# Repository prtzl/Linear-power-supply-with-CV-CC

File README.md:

# Linear-power-supply-with-CC-CV

 Self made Linear power supply based on ThePostApocalypticInventor's work. Details in schematic and readme.
  
I made this schematic based on The Post Apocalyptic Inventor's work, that you can find in his chanel https://www.youtube.com/channel/UCDbWmfrwmzn1ZsGgrYRUxoA

This power supply design has been rewritten, tested and built by me and in the future, there will be pictures and videos of the finished project.

The power supply is very simple to make and to understand, so for any questions you can visit his video (https://www.youtube.com/watch?v=_CFIovMkRyg) describing all parts of the power supply. Feel free to ask him or me for advice.

Also this project involves mains power and mishandling of it can be fatal so make sure that you know that are you doing, buy premade mains components, such as the transformer and mains input with **fuse**.
## Warning
 **I am not responsible for any damage to your equipment or your health so study the circuit, and if you work with wiring your own mains part, make sure that you know what you are doing and so at your own risk.**
  
  Happy making! :P

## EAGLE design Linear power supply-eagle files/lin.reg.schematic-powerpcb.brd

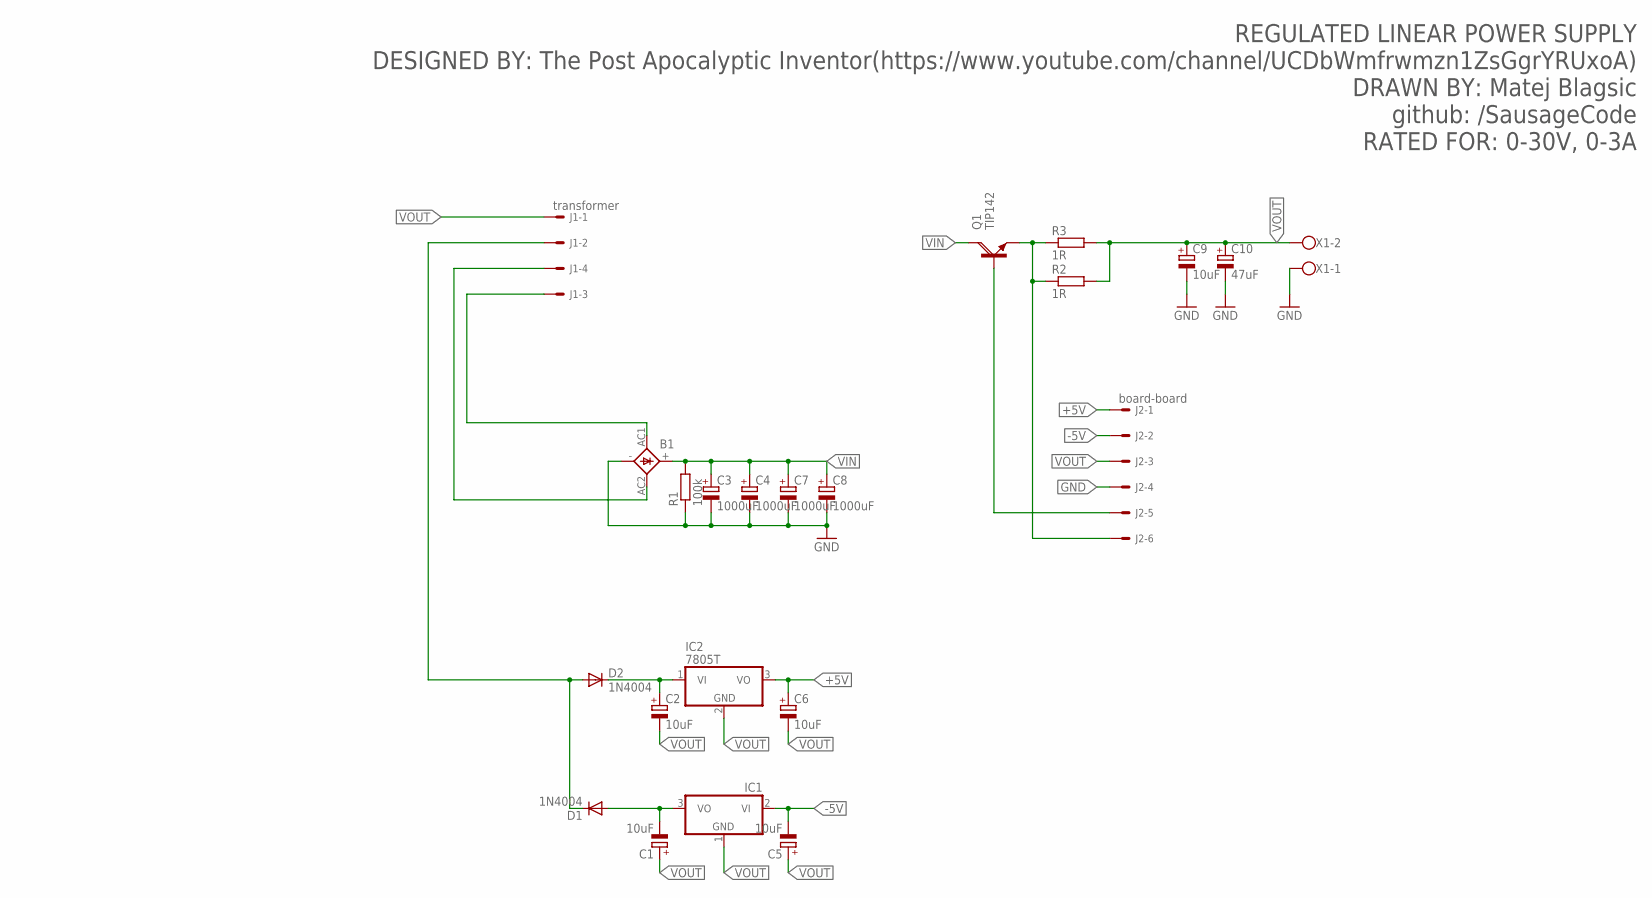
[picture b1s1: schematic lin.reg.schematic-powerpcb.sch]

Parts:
B1: 2KBB-R
C1, C2, C5, C6, C9: 10uF; E2-5
C3, C4, C7, C8: 1000uF; E5-13
C10: 47uF; E2-5
D1, D2: 1N4004; DO41-10
IC1: 7905T; TO220H
IC2: 7805T; TO220H
J1: transformer; 6410-04
J2: board-board; 6410-06
Q1: TIP142; SOT93
R1: 100k; 0309/12
R2, R3: 1R; 0922/22
X1: W237-102

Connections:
+5V: C6.+, IC2.3 (VO), J2.1
-5V: C5.-, IC1.2 (VI), J2.2
GND: B1.-, C3.-, C4.-, C7.-, C8.-, C9.-, C10.-, J2.4, R1.1, X1.1
unnamed: J2.6, Q1.E, R2.1, R3.1
unnamed: J2.5, Q1.B
unnamed: C2.+, D2.C, IC2.1 (VI)
unnamed: C1.-, D1.A, IC1.3 (VO)
unnamed: D1.C, D2.A, J1.2
unnamed: B1.AC2, J1.4
unnamed: B1.AC1, J1.3
VIN: B1.+, C3.+, C4.+, C7.+, C8.+, Q1.C, R1.2
VOUT: C1.+, C2.-, C5.+, C6.-, C9.+, C10.+, IC1.1 (GND), IC2.2 (GND), J1.1, J2.3, R2.2, R3.2, X1.2

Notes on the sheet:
REGULATED LINEAR POWER SUPPLY DESIGNED BY: The Post Apocalyptic Inventor(https://www.youtube.com/channel/UCDbWmfrwmzn1ZsGgrYRUxoA) DRAWN BY: Matej Blagsic github: /SausageCode RATED FOR: 0-30V, 0-3A

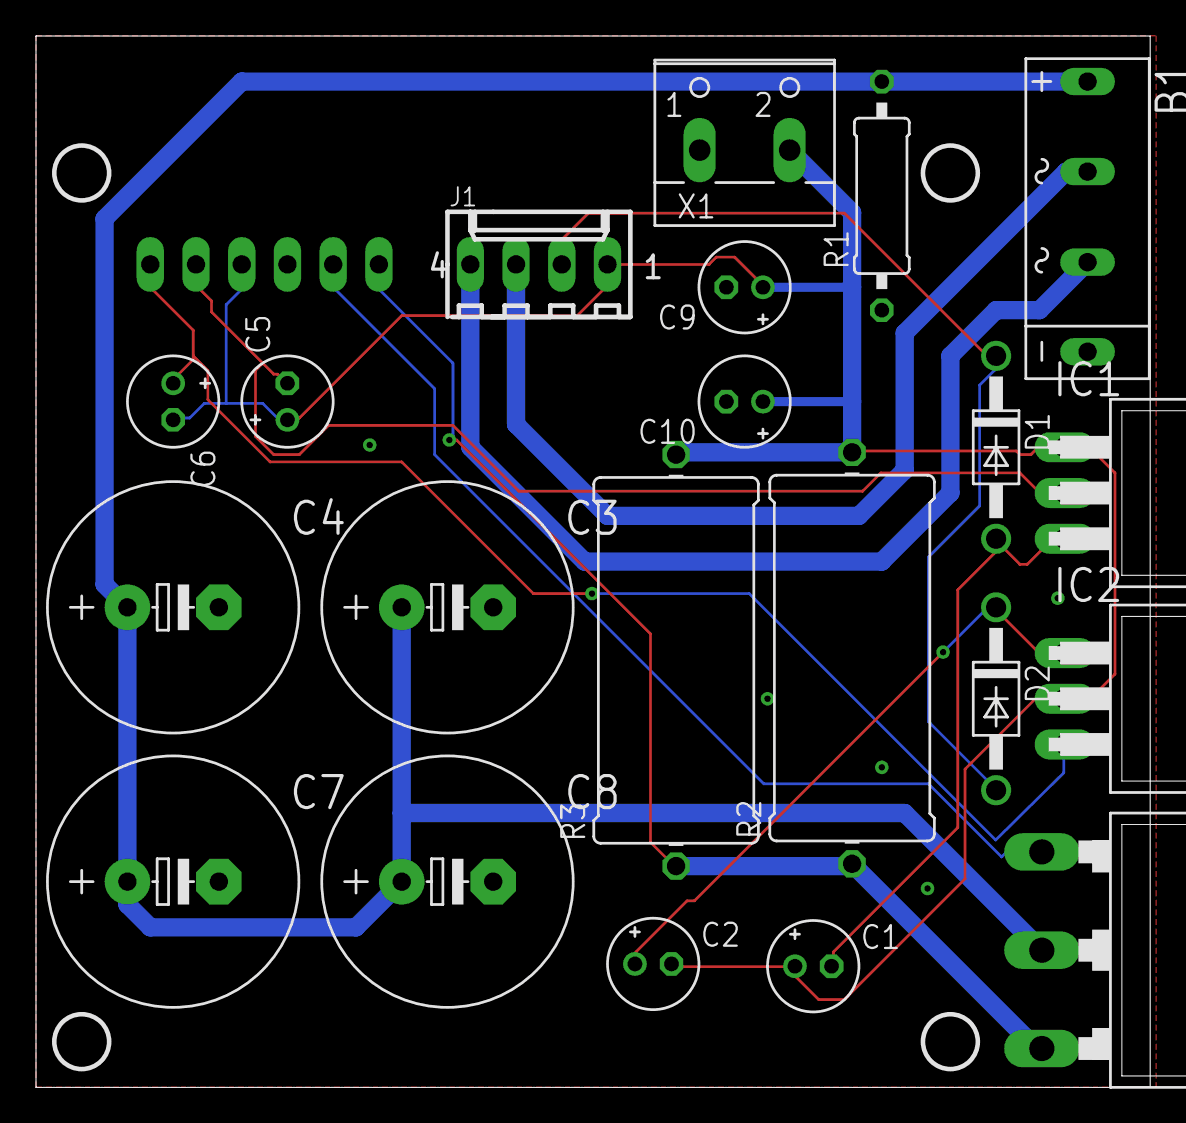
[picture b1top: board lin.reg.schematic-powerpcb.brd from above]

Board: 2 copper layers, 61.9 x 58.4 mm, 22 parts (1 on the bottom side), 12 nets.

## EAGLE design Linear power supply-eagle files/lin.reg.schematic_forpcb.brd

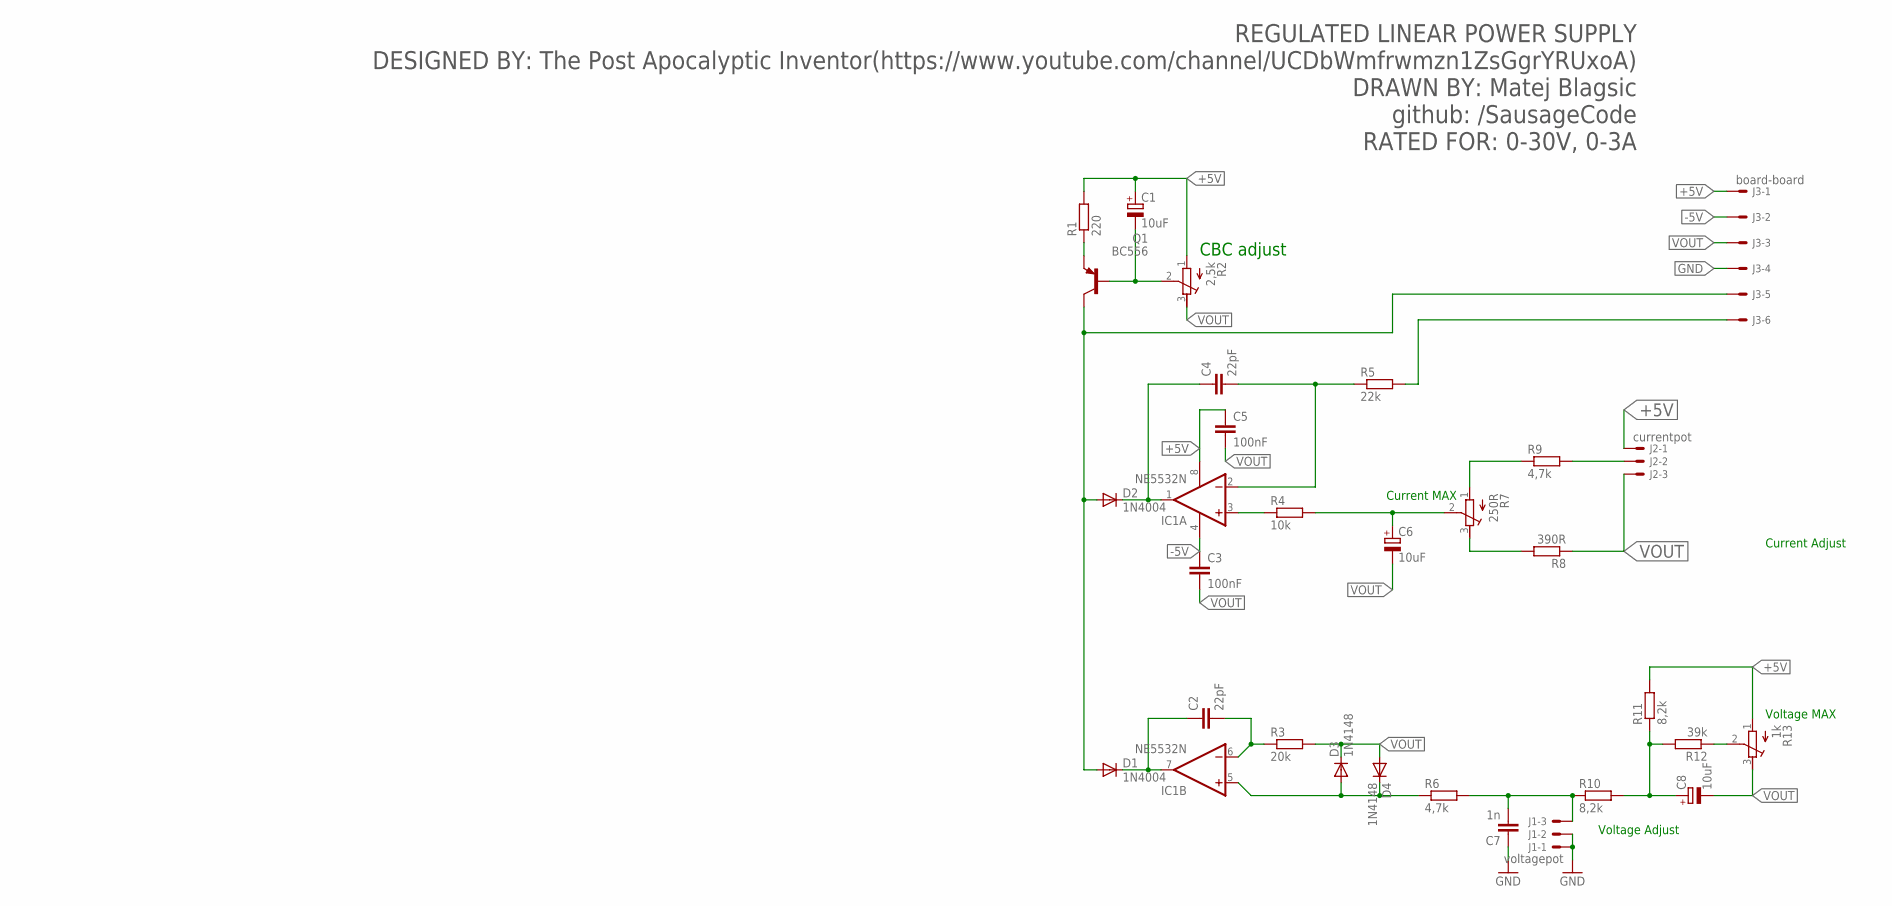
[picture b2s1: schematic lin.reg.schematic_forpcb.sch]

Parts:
C1, C6, C8: 10uF; E2,5-5
C2, C4: 22pF; C025-025X050
C3, C5: 100nF; C025-025X050
C7: 1n; C025-025X050
D1, D2: 1N4004; DO41-10
D3, D4: 1N4148; DO41-10
IC1: NE5532N; DIL08
J1: voltagepot; 6410-03
J2: currentpot; 6410-03
J3: board-board; 6410-06
Q1: BC556; TO92-EBC
R1: 220; 0207/10
R2: 2,5k; RTRIM64W
R3: 20k; 0207/10
R4: 10k; 0207/10
R5: 22k; 0207/10
R6, R9: 4,7k; 0207/10
R7: 250R; RTRIM64W
R8: 390R; 0207/10
R10, R11: 8,2k; 0207/10
R12: 39k; 0207/10
R13: 1k; RTRIM64W

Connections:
+5V: C1.+, C5.1, IC1.8 (V+), J2.1, J3.1, R1.2, R2.1 (A), R11.2, R13.1 (A)
-5V: C3.1, IC1.4 (V-), J3.2
GND: C7.1, J1.1, J1.2, J3.4
unnamed: C1.-, Q1.B, R2.2 (S)
unnamed: Q1.E, R1.1
unnamed: R7.1 (A), R9.1
unnamed: C4.1, D2.C, IC1.1 (OUT)
unnamed: C2.1, D1.C, IC1.7 (OUT)
unnamed: D1.A, D2.A, J3.5, Q1.C
unnamed: C2.2, IC1.6 (-IN), R3.1
unnamed: IC1.3 (+IN), R4.1
unnamed: D3.A, D4.C, IC1.5 (+IN), R6.1
unnamed: R7.3 (E), R8.2
unnamed: J2.2, R9.2
unnamed: C6.+, R4.2, R7.2 (S)
unnamed: C4.2, IC1.2 (-IN), R5.1
unnamed: C7.2, J1.3, R6.2, R10.1
unnamed: C8.+, R10.2, R11.1, R12.2
unnamed: R12.1, R13.2 (S)
unnamed: J3.6, R5.2
VOUT: C3.2, C5.2, C6.-, C8.-, D3.C, D4.A, J2.3, J3.3, R2.3 (E), R3.2, R8.1, R13.3 (E)

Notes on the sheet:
Voltage Adjust
Voltage MAX
Current Adjust
Current MAX
REGULATED LINEAR POWER SUPPLY DESIGNED BY: The Post Apocalyptic Inventor(https://www.youtube.com/channel/UCDbWmfrwmzn1ZsGgrYRUxoA) DRAWN BY: Matej Blagsic github: /SausageCode RATED FOR: 0-30V, 0-3A
CBC adjust

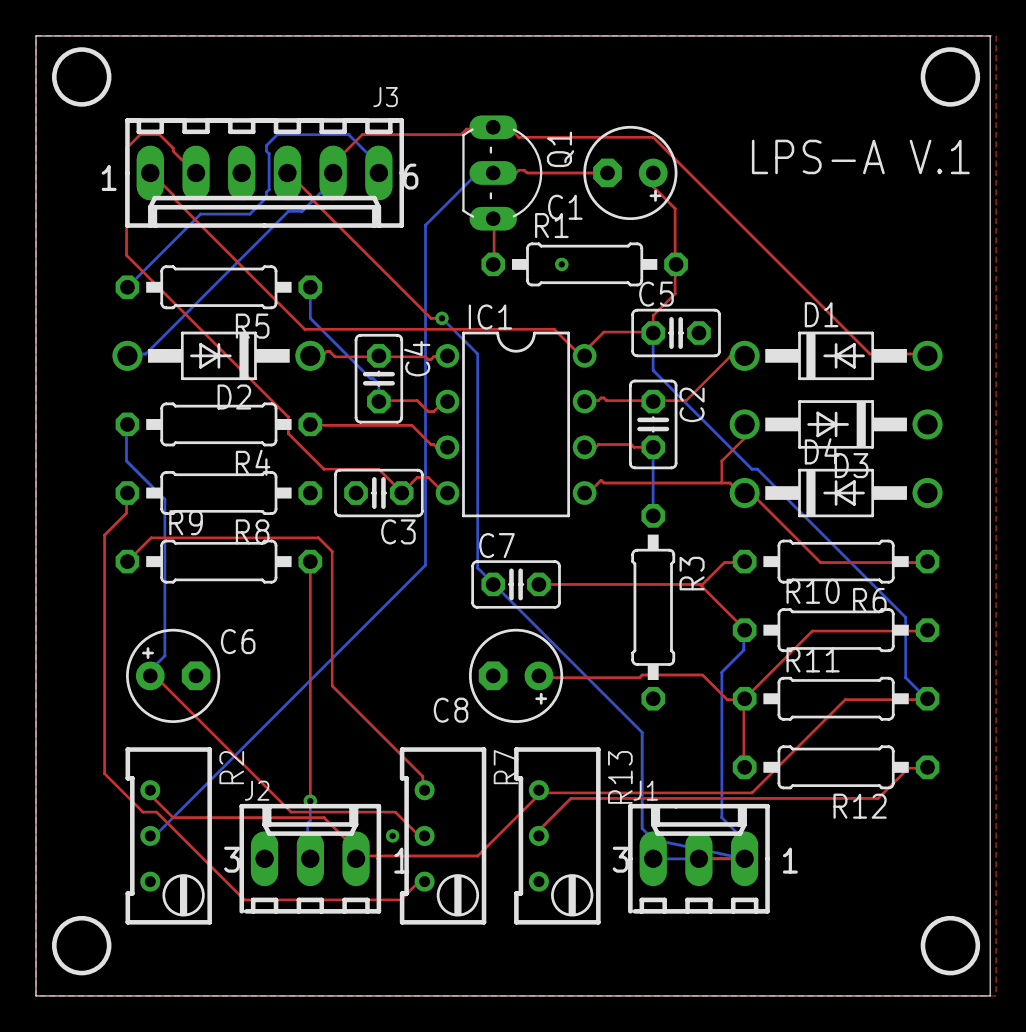
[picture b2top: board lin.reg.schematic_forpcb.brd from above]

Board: 2 copper layers, 53.0 x 53.3 mm, 30 parts (0 on the bottom side), 21 nets.

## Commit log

2018-01-02 first
